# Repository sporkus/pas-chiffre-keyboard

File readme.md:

# ceci n'est pas le chiffre
================================

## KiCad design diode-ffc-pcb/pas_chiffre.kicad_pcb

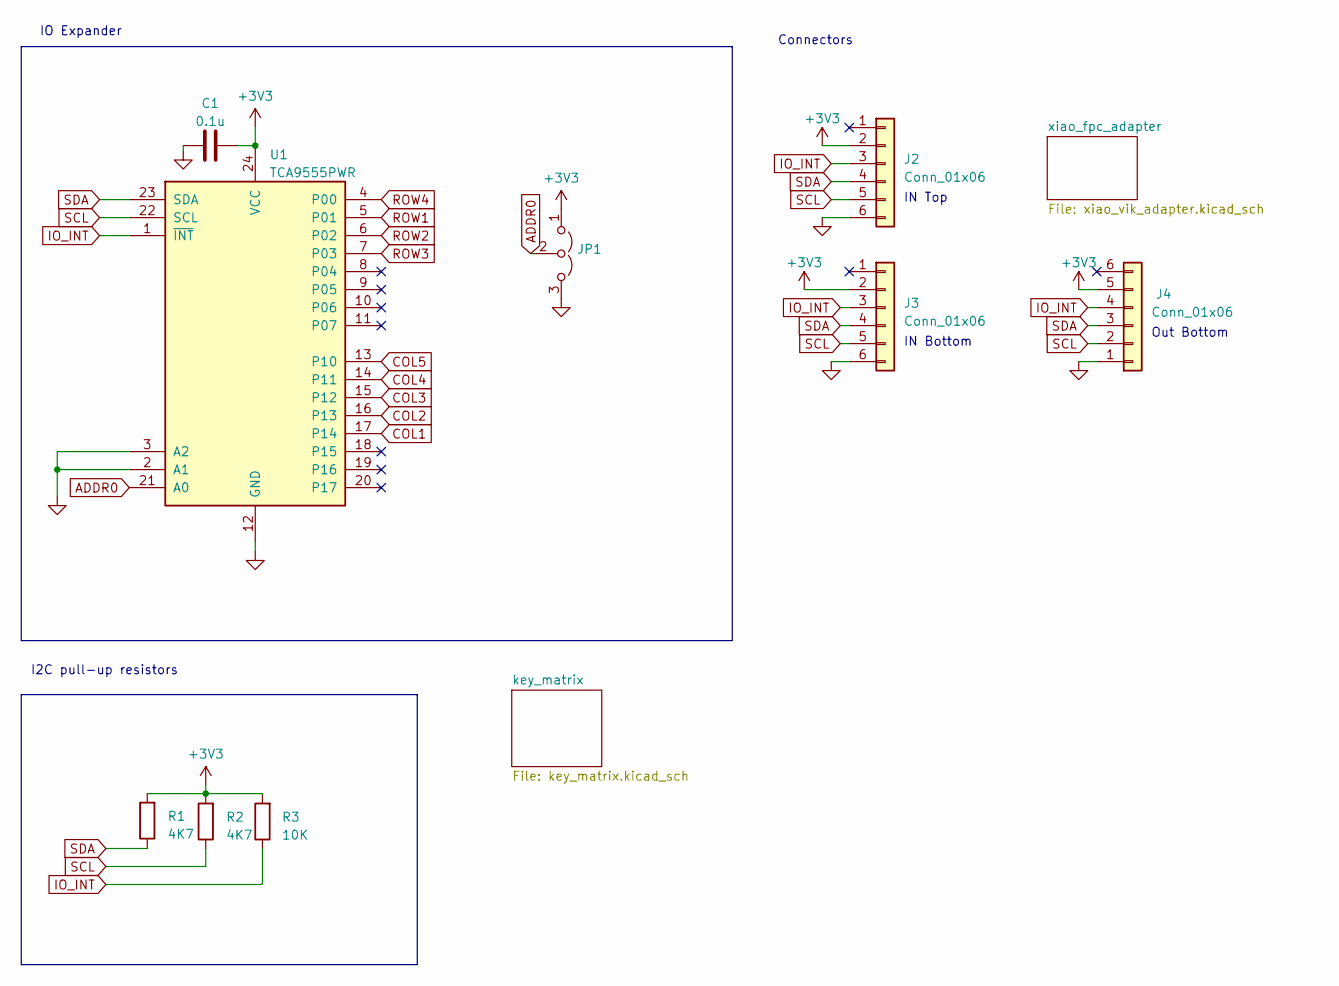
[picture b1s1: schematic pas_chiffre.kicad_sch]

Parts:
C1: 0.1u; C_0402_1005Metric_Pad0.74x0.62mm_HandSolder
J2, J3, J4: Conn_01x06; Hirose_FH12-6S-0.5SH_1x06-1MP_P0.50mm_Horizontal
JP1: Jumper_3_Open; SolderJumper-3_P1.3mm_Open_RoundedPad1.0x1.5mm
R1, R2: 4K7; R_0805_2012Metric_Pad1.20x1.40mm_HandSolder
R3: 10K; R_0805_2012Metric_Pad1.20x1.40mm_HandSolder
U1: TCA9555PWR; TSSOP-24_4.4x7.8mm_P0.65mm

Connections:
+3V3: C1.2, J2.2, J3.2, J4.5, JP1.1 (A), R1.2, R2.2, R3.2, U1.24 (VCC); also elsewhere on the board
ADDR0: JP1.2 (C), U1.21 (A0)
COL1: U1.17 (P14); also elsewhere on the board
COL2: U1.16 (P13); also elsewhere on the board
COL3: U1.15 (P12); also elsewhere on the board
COL4: U1.14 (P11); also elsewhere on the board
COL5: U1.13 (P10); also elsewhere on the board
GND: C1.1, J2.6, J3.6, J4.1, JP1.3 (B), U1.2 (A1), U1.3 (A2), U1.12 (GND); also elsewhere on the board
IO_INT: J2.3, J3.3, J4.4, R3.1, U1.1 (~INT); also elsewhere on the board
ROW1: U1.5 (P01); also elsewhere on the board
ROW2: U1.6 (P02); also elsewhere on the board
ROW3: U1.7 (P03); also elsewhere on the board
ROW4: U1.4 (P00); also elsewhere on the board
SCL: J2.5, J3.5, J4.2, R2.1, U1.22 (SCL); also elsewhere on the board
SDA: J2.4, J3.4, J4.3, R1.1, U1.23 (SDA); also elsewhere on the board

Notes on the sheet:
I2C pull-up resistors
IO Expander
IN Bottom
Out Bottom
Connectors
IN Top

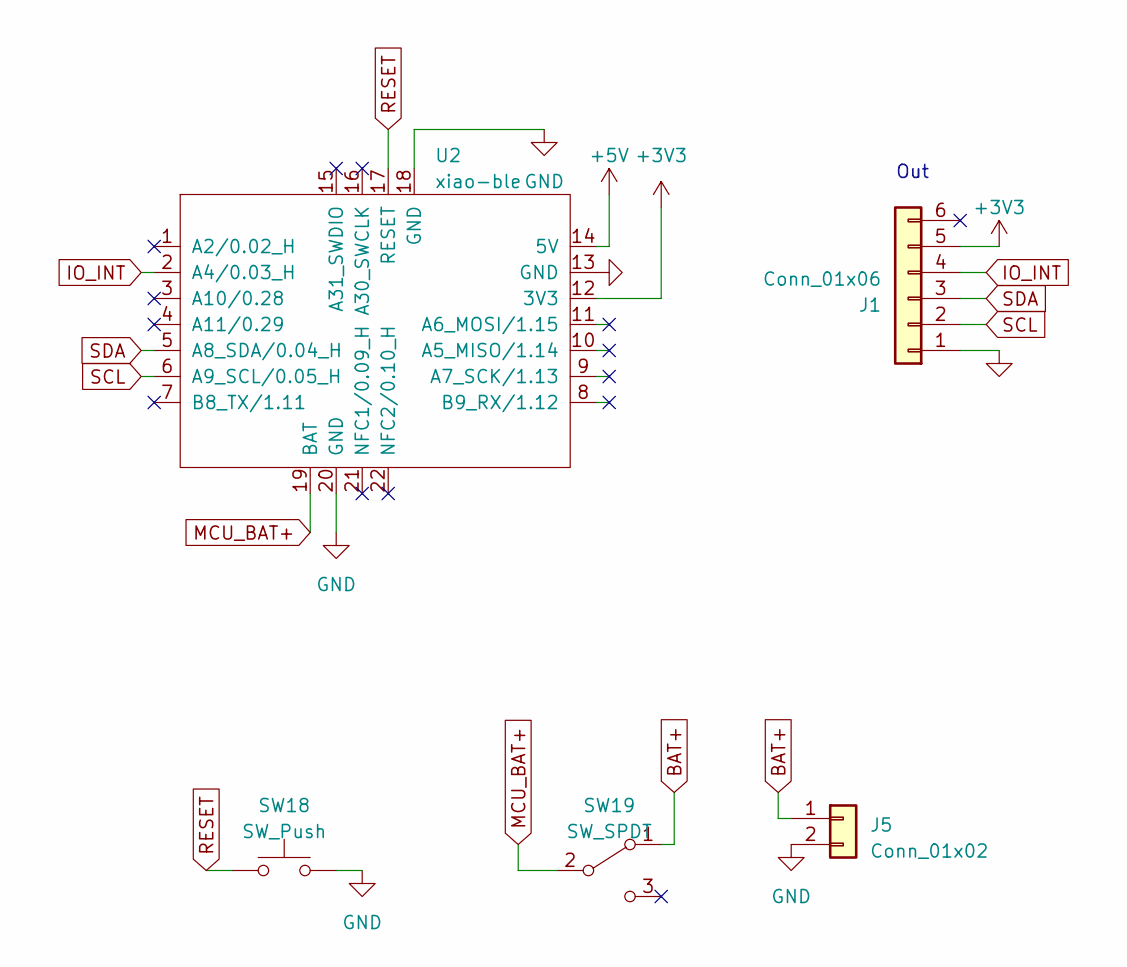
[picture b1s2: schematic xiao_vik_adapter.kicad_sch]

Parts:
J1: Conn_01x06; Hirose_FH12-6S-0.5SH_1x06-1MP_P0.50mm_Horizontal
J5: Conn_01x02; JST_PH_S2B-PH-K_1x02_P2.00mm_Horizontal
SW18: SW_Push; SW_SPST_SKQG_WithStem
SW19: SW_SPDT; switch-MSK-12C02-smd
U2: xiao-ble; xiao-ble-tht-bodge

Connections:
+3V3: J1.5, U2.12 (3V3); also elsewhere on the board
+5V: U2.14 (5V)
BAT+: J5.1, SW19.1 (A)
GND: J1.1, J5.2, SW18.2, U2.13 (GND), U2.18 (GND), U2.20 (GND); also elsewhere on the board
IO_INT: J1.4, U2.2 (A4/0.03_H); also elsewhere on the board
MCU_BAT+: SW19.2 (B), U2.19 (BAT)
RESET: SW18.1, U2.17 (RESET)
SCL: J1.2, U2.6 (A9_SCL/0.05_H); also elsewhere on the board
SDA: J1.3, U2.5 (A8_SDA/0.04_H); also elsewhere on the board

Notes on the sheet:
Out

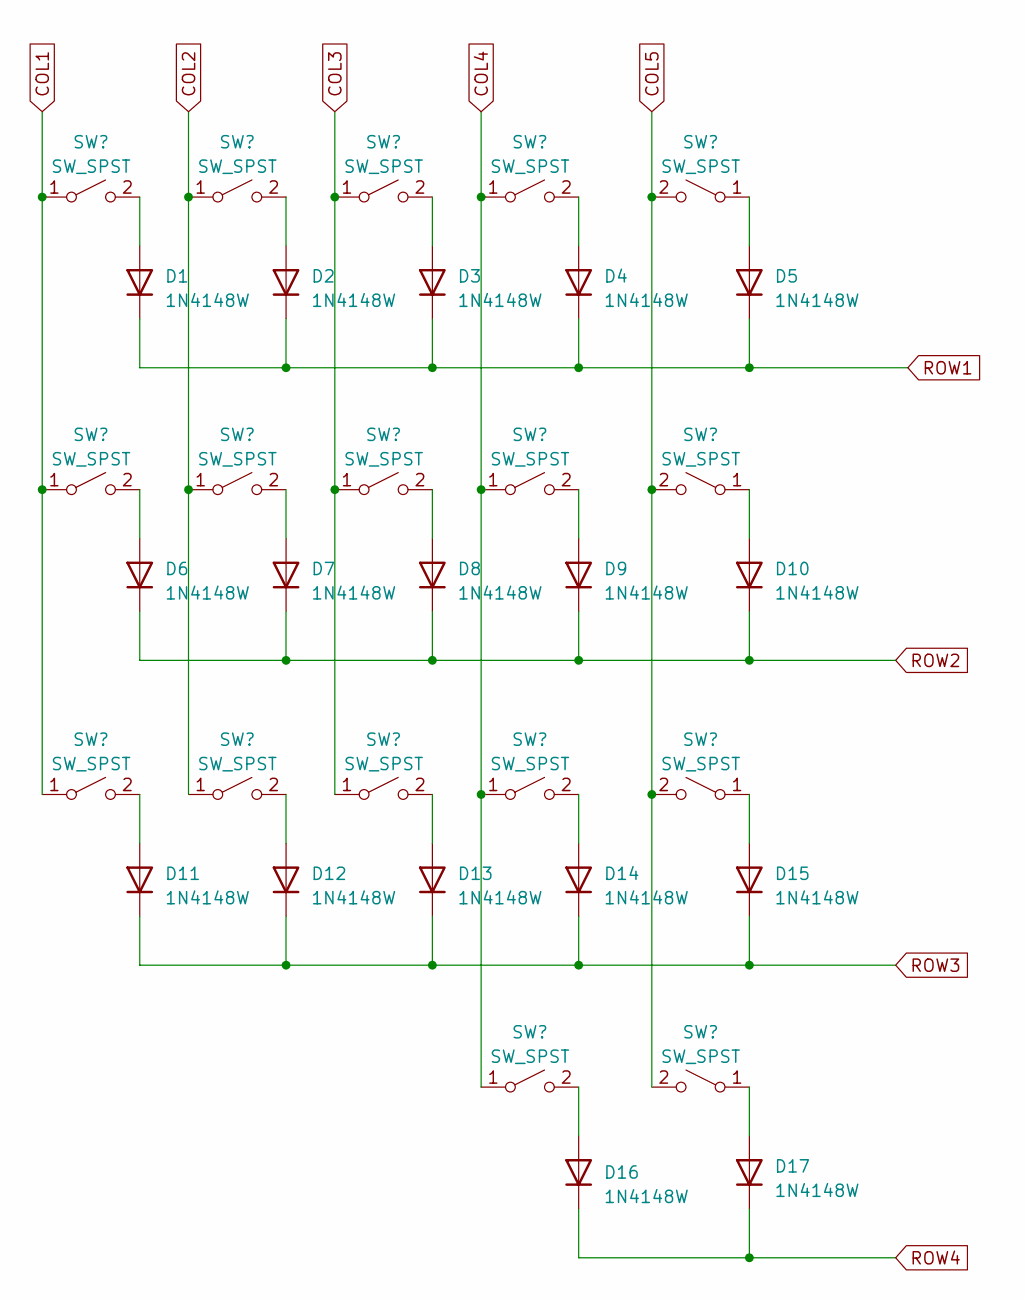
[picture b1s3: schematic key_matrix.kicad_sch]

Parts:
D1, D2, D3, D4, D5, D6, D7, D8, D9, D10, D11, D12, D13, D14, D15, D16, D17: 1N4148W; D_SOD-123
SW1, SW2, SW3, SW4, SW5, SW6, SW7, SW8, SW9, SW10, SW11, SW12, SW13, SW14, SW15, SW16, SW17: SW_SPST; SW_MX_reversible

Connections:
COL1: SW1.1 (A), SW6.1 (A), SW11.1 (A); also elsewhere on the board
COL2: SW2.1 (A), SW7.1 (A), SW12.1 (A); also elsewhere on the board
COL3: SW3.1 (A), SW8.1 (A), SW13.1 (A); also elsewhere on the board
COL4: SW4.1 (A), SW9.1 (A), SW14.1 (A), SW16.1 (A); also elsewhere on the board
COL5: SW5.2 (B), SW10.2 (B), SW15.2 (B), SW17.2 (B); also elsewhere on the board
unnamed: D1.2 (A), SW1.2 (B)
unnamed: D2.2 (A), SW2.2 (B)
unnamed: D3.2 (A), SW3.2 (B)
unnamed: D4.2 (A), SW4.2 (B)
unnamed: D5.2 (A), SW5.1 (A)
unnamed: D6.2 (A), SW6.2 (B)
unnamed: D7.2 (A), SW7.2 (B)
unnamed: D8.2 (A), SW8.2 (B)
unnamed: D9.2 (A), SW9.2 (B)
unnamed: D10.2 (A), SW10.1 (A)
unnamed: D11.2 (A), SW11.2 (B)
unnamed: D12.2 (A), SW12.2 (B)
unnamed: D13.2 (A), SW13.2 (B)
unnamed: D14.2 (A), SW14.2 (B)
unnamed: D15.2 (A), SW15.1 (A)
unnamed: D16.2 (A), SW16.2 (B)
unnamed: D17.2 (A), SW17.1 (A)
ROW1: D1.1 (K), D2.1 (K), D3.1 (K), D4.1 (K), D5.1 (K); also elsewhere on the board
ROW2: D6.1 (K), D7.1 (K), D8.1 (K), D9.1 (K), D10.1 (K); also elsewhere on the board
ROW3: D11.1 (K), D12.1 (K), D13.1 (K), D14.1 (K), D15.1 (K); also elsewhere on the board
ROW4: D16.1 (K), D17.1 (K); also elsewhere on the board

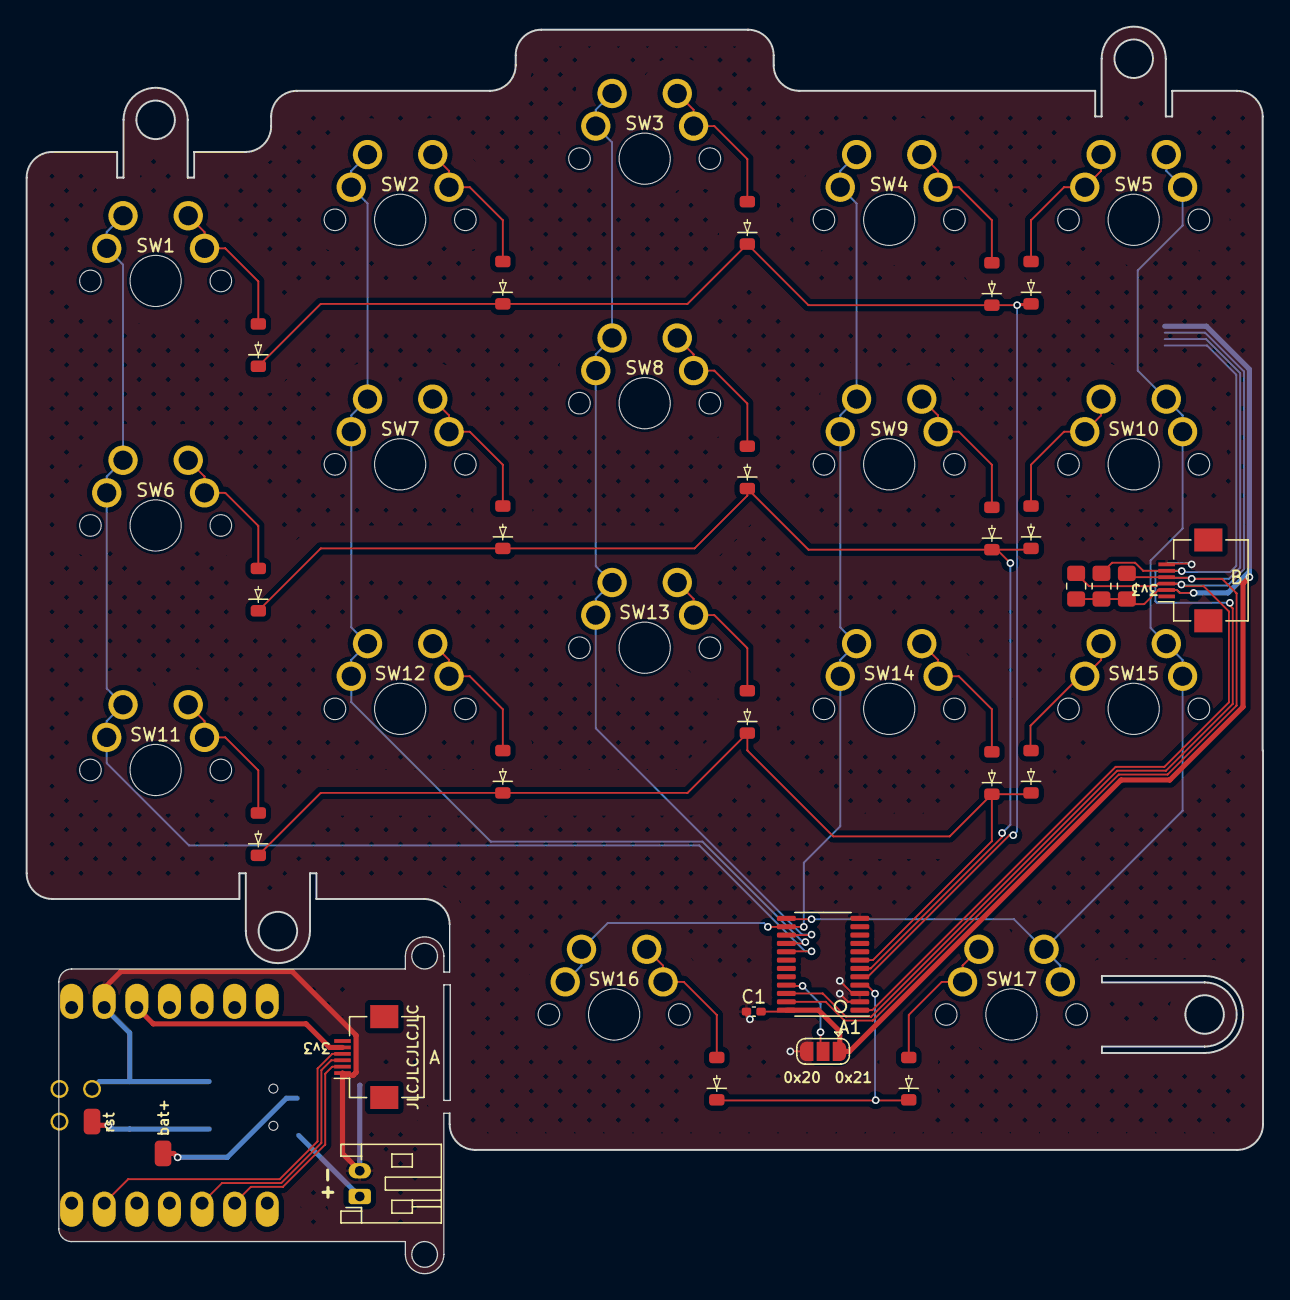
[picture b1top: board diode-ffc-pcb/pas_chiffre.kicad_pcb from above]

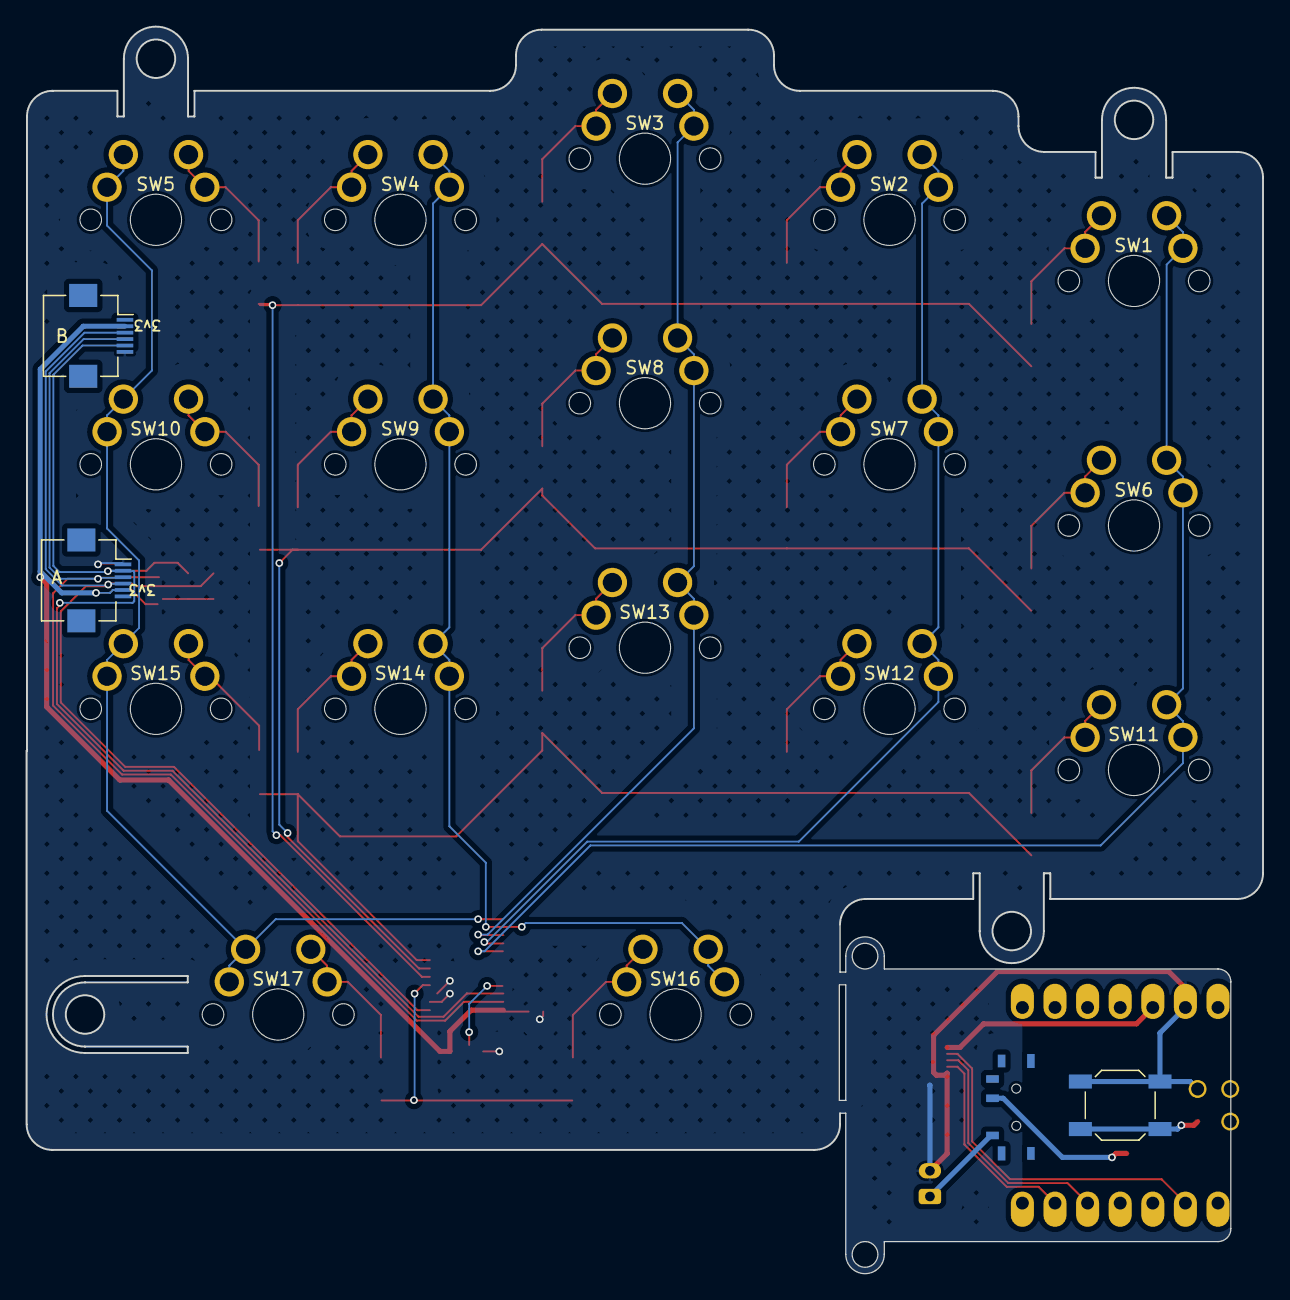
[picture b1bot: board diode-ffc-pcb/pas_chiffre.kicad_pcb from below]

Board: 2 copper layers, 96.3 x 97.1 mm, 48 parts (4 on the bottom side), 35 nets.

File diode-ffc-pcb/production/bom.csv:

Designator,Footprint,Quantity,Value,LCSC Part #
C1,0402,1,0.1u,
"D1, D10, D11, D12, D13, D14, D15, D16, D17, D2, D3, D4, D5, D6, D7, D8, D9",D_SOD-123,17,1N4148W,
"J1, J2, J3, J4",Hirose_FH12-6S-0.5SH_1x06-1MP_P0.50mm_Horizontal,4,Conn_01x06,
J5,JST_PH_S2B-PH-K_1x02_P2.00mm_Horizontal,1,Conn_01x02,
JP1,SolderJumper-3_P1.3mm_Open_RoundedPad1.0x1.5mm,1,Jumper_3_Open,
"R1, R2",0805,2,4K7,
R3,0805,1,10K,
"SW1, SW10, SW11, SW12, SW13, SW14, SW15, SW16, SW17, SW2, SW3, SW4, SW5, SW6, SW7, SW8, SW9",SW_MX_reversible,17,SW_SPST,
SW18,SW_SPST_SKQG_WithStem,1,SW_Push,
SW19,switch-MSK-12C02-smd,1,SW_SPDT,
U1,TSSOP-24_4.4x7.8mm_P0.65mm,1,TCA9555PWR,
U2,xiao-ble-tht-bodge,1,xiao-ble,

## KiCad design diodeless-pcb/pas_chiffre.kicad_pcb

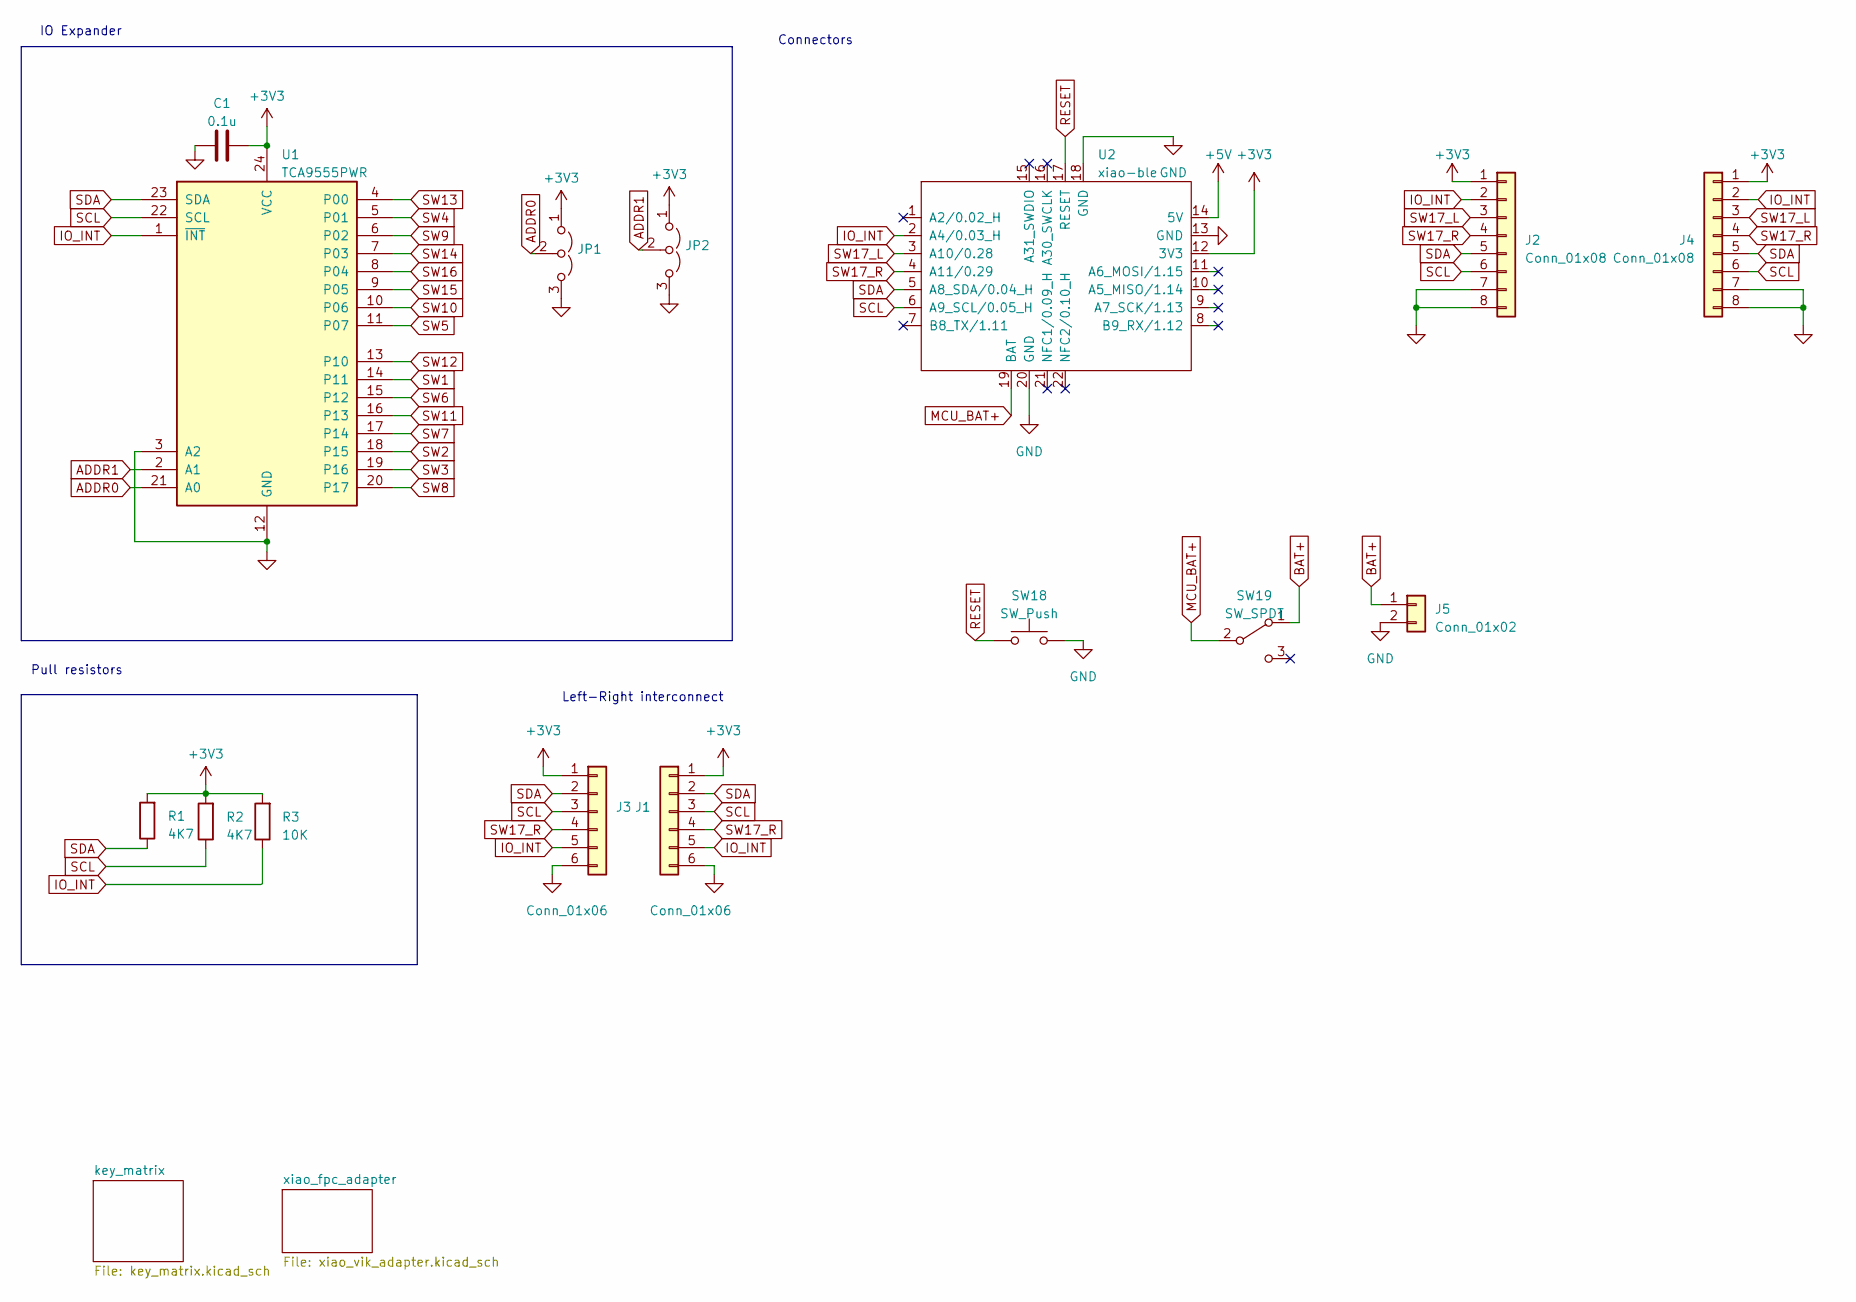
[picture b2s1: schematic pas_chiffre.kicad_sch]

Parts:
C1: 0.1u; Molex_200528-0060_1x06-1MP_P1.00mm_Horizontal
J1, J3: Conn_01x06; TE_84952-6_1x06-1MP_P1.0mm_Horizontal
J2, J4: Conn_01x08; TE_84952-8_1x08-1MP_P1.0mm_Horizontal
J5: Conn_01x02; PinHeader_1x02_P1.00mm_Horizontal
JP1, JP2: Jumper_3_Open; SolderJumper-3_P1.3mm_Open_Pad1.0x1.5mm
R1, R2: 4K7; R_0805_2012Metric_Pad1.20x1.40mm_HandSolder
R3: 10K; R_0805_2012Metric_Pad1.20x1.40mm_HandSolder
SW18: SW_Push; SW_SPST_SKQG_WithStem
SW19: SW_SPDT; switch-MSK-12C02-smd
U1: TCA9555PWR; TSSOP-24_4.4x7.8mm_P0.65mm
U2: xiao-ble; xiao-ble-tht-bodge

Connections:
+3V3: C1.2, J1.1, J2.1, J3.1, J4.1, JP1.1 (A), JP2.1 (A), R1.2, R2.2, R3.2, U1.24 (VCC), U2.12 (3V3)
+5V: U2.14 (5V)
ADDR0: JP1.2 (C), U1.21 (A0)
ADDR1: JP2.2 (C), U1.2 (A1)
BAT+: J5.1, SW19.1 (A)
GND: C1.1, J1.6, J2.7, J2.8, J3.6, J4.7, J4.8, J5.2, JP1.3 (B), JP2.3 (B), SW18.2, U1.3 (A2), U1.12 (GND), U2.13 (GND), U2.18 (GND), U2.20 (GND); also elsewhere on the board
IO_INT: J1.5, J2.2, J3.5, J4.2, R3.1, U1.1 (~INT), U2.2 (A4/0.03_H)
MCU_BAT+: SW19.2 (B), U2.19 (BAT)
RESET: SW18.1, U2.17 (RESET)
SCL: J1.3, J2.6, J3.3, J4.6, R2.1, U1.22 (SCL), U2.6 (A9_SCL/0.05_H)
SDA: J1.2, J2.5, J3.2, J4.5, R1.1, U1.23 (SDA), U2.5 (A8_SDA/0.04_H)
SW1: U1.14 (P11); also elsewhere on the board
SW2: U1.18 (P15); also elsewhere on the board
SW3: U1.19 (P16); also elsewhere on the board
SW4: U1.5 (P01); also elsewhere on the board
SW5: U1.11 (P07); also elsewhere on the board
SW6: U1.15 (P12); also elsewhere on the board
SW7: U1.17 (P14); also elsewhere on the board
SW8: U1.20 (P17); also elsewhere on the board
SW9: U1.6 (P02); also elsewhere on the board
SW10: U1.10 (P06); also elsewhere on the board
SW11: U1.16 (P13); also elsewhere on the board
SW12: U1.13 (P10); also elsewhere on the board
SW13: U1.4 (P00); also elsewhere on the board
SW14: U1.7 (P03); also elsewhere on the board
SW15: U1.9 (P05); also elsewhere on the board
SW16: U1.8 (P04); also elsewhere on the board
SW17_L: J2.3, J4.3, U2.3 (A10/0.28); also elsewhere on the board
SW17_R: J1.4, J2.4, J3.4, J4.4, U2.4 (A11/0.29); also elsewhere on the board

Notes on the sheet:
Pull resistors
Left-Right interconnect
IO Expander
Connectors

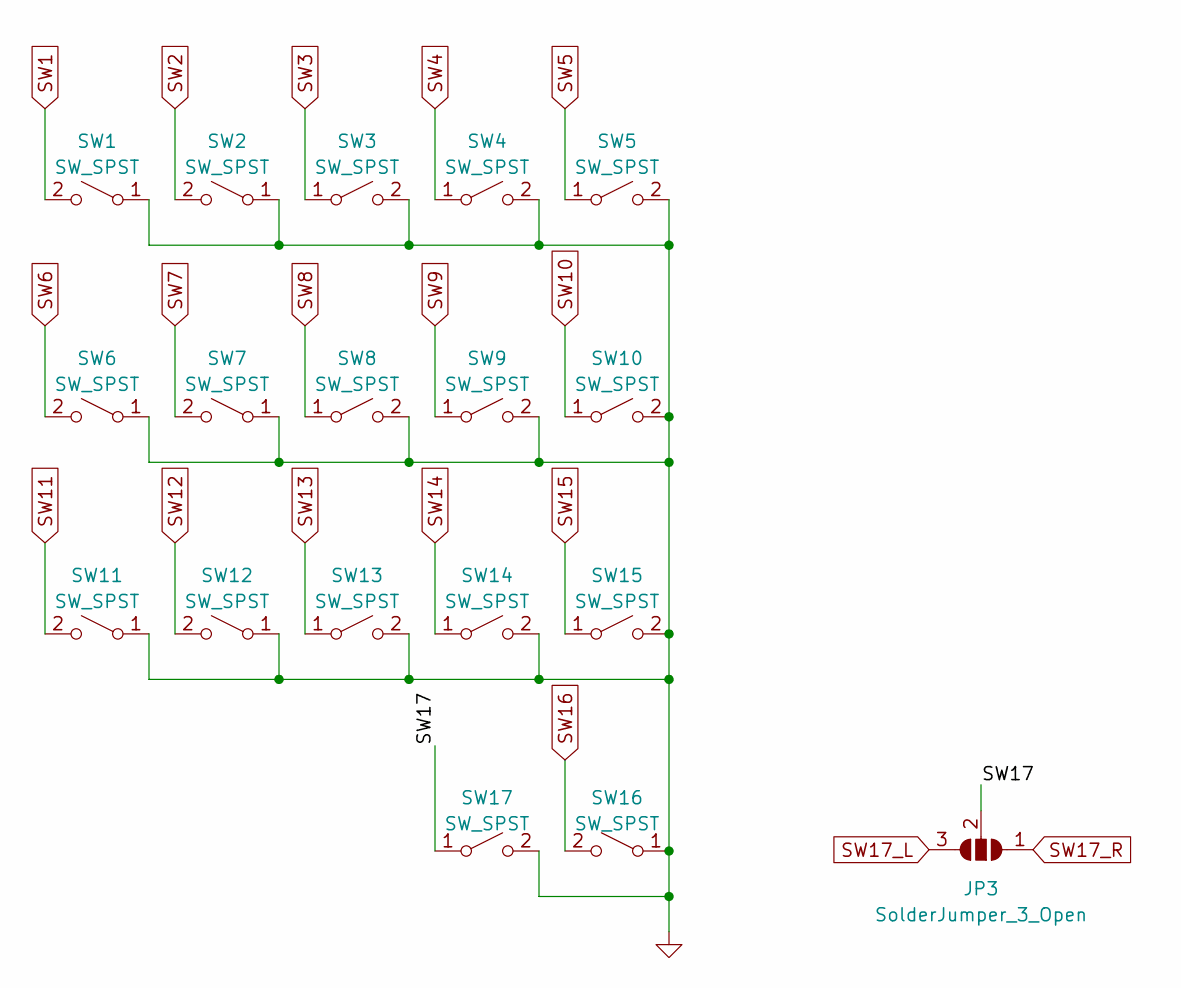
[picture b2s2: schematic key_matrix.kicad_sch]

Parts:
JP3: SolderJumper_3_Open; SolderJumper-3_P1.3mm_Open_RoundedPad1.0x1.5mm
SW1, SW2, SW3, SW4, SW5, SW6, SW7, SW8, SW9, SW10, SW11, SW12, SW13, SW14, SW15, SW16, SW17: SW_SPST; SW_MX_reversible

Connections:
/key_matrix/SW17: JP3.2 (C), SW17.1 (A)
GND: SW1.1 (A), SW2.1 (A), SW3.2 (B), SW4.2 (B), SW5.2 (B), SW6.1 (A), SW7.1 (A), SW8.2 (B), SW9.2 (B), SW10.2 (B), SW11.1 (A), SW12.1 (A), SW13.2 (B), SW14.2 (B), SW15.2 (B), SW16.1 (A), SW17.2 (B); also elsewhere on the board
SW1: SW1.2 (B); also elsewhere on the board
SW2: SW2.2 (B); also elsewhere on the board
SW3: SW3.1 (A); also elsewhere on the board
SW4: SW4.1 (A); also elsewhere on the board
SW5: SW5.1 (A); also elsewhere on the board
SW6: SW6.2 (B); also elsewhere on the board
SW7: SW7.2 (B); also elsewhere on the board
SW8: SW8.1 (A); also elsewhere on the board
SW9: SW9.1 (A); also elsewhere on the board
SW10: SW10.1 (A); also elsewhere on the board
SW11: SW11.2 (B); also elsewhere on the board
SW12: SW12.2 (B); also elsewhere on the board
SW13: SW13.1 (A); also elsewhere on the board
SW14: SW14.1 (A); also elsewhere on the board
SW15: SW15.1 (A); also elsewhere on the board
SW16: SW16.2 (B); also elsewhere on the board
SW17_L: JP3.3 (B); also elsewhere on the board
SW17_R: JP3.1 (A); also elsewhere on the board

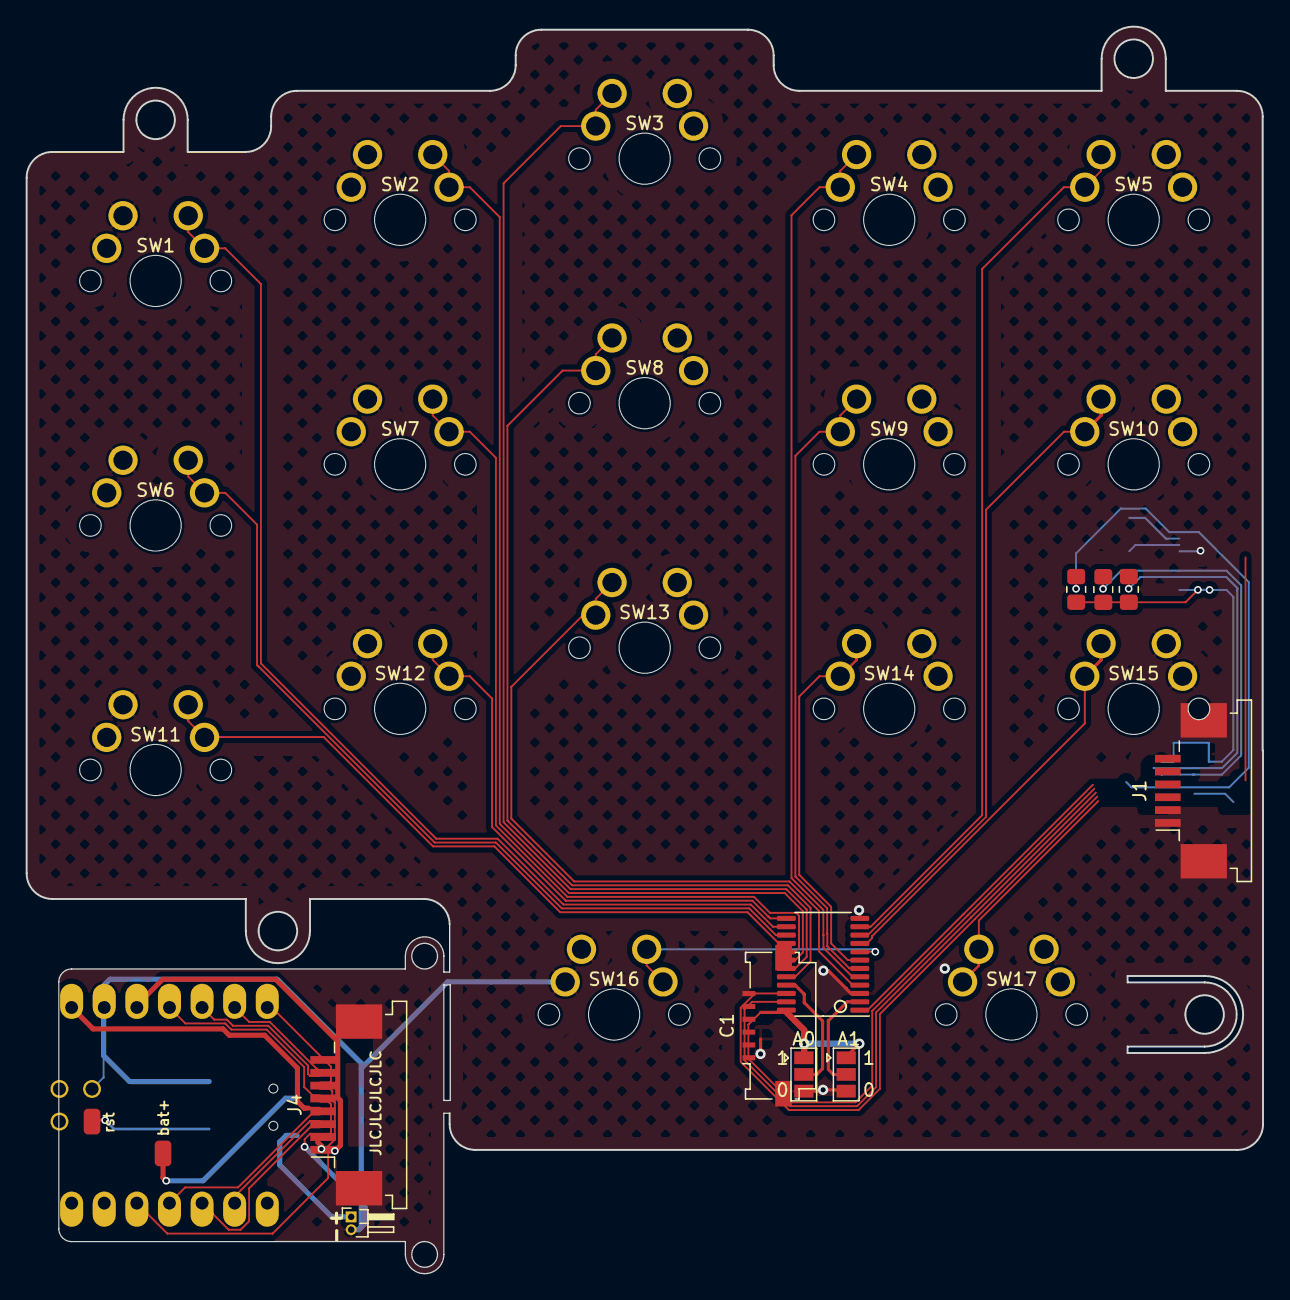
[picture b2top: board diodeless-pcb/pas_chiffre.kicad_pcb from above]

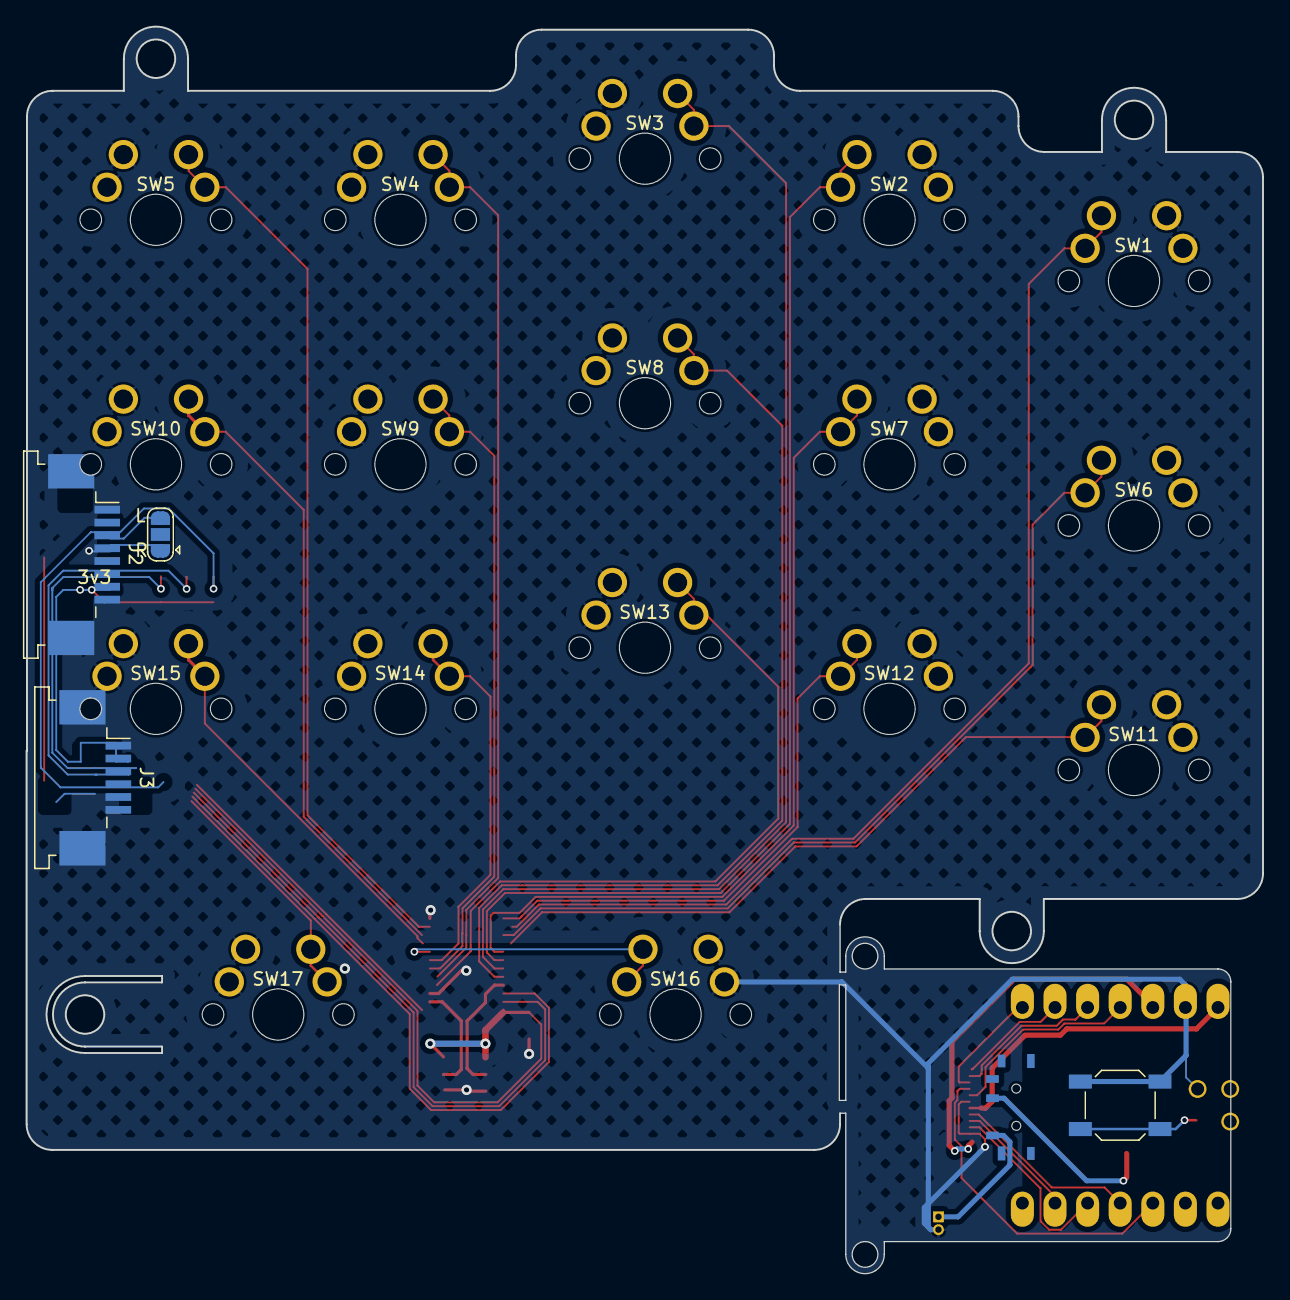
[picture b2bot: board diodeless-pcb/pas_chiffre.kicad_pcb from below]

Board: 2 copper layers, 96.3 x 97.1 mm, 33 parts (5 on the bottom side), 29 nets.

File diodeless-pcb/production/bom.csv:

Designator,Footprint,Quantity,Value,LCSC Part #
C1,0805,1,0.1u,
"J1, J3",conn_01x06_P0.50mm,2,Conn_01x06,
J2,conn_01x12_P0.50mm,1,~,
J4,vik-keyboard-connector-horizontal,1,~,
J5,PinHeader_1x02_P1.00mm_Horizontal,1,Conn_01x02,
"JP1, JP2",SolderJumper-3_P1.3mm_Open_Pad1.0x1.5mm,2,Jumper_3_Open,
JP3,SolderJumper-3_P1.3mm_Open_RoundedPad1.0x1.5mm,1,SolderJumper_3_Open,
"R1, R2",0805,2,4K7,
R3,0805,1,10K,
"SW1, SW10, SW11, SW12, SW13, SW14, SW15, SW16, SW17, SW2, SW3, SW4, SW5, SW6, SW7, SW8, SW9",SW_MX_reversible,17,SW_SPST,
SW18,SW_SPST_SKQG_WithStem,1,SW_Push,
SW19,switch-MSK-12C02-smd,1,SW_SPDT,
U1,TSSOP-24_4.4x7.8mm_P0.65mm,1,TCA9555PWR,
U2,xiao-ble-tht-bodge,1,xiao-ble,

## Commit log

2023-06-02 init
2023-06-02 reshuffling
2023-06-02 updated gerber
2023-06-02 fixed switch footprint
2023-06-12 version sent for production
2023-07-03 messing around
